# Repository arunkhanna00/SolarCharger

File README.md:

# Solar Charger

Using this PCB, you can charge a LiPo/Li-Ion battery with a solar panel and get a +5V voltage source. Additional features include:

- short circuit protection
- over charging/discharging protection
- MPPT

The voltage range for the input solar panel is 4-28 V.

The maximum current drawn from battery is around 800 mA

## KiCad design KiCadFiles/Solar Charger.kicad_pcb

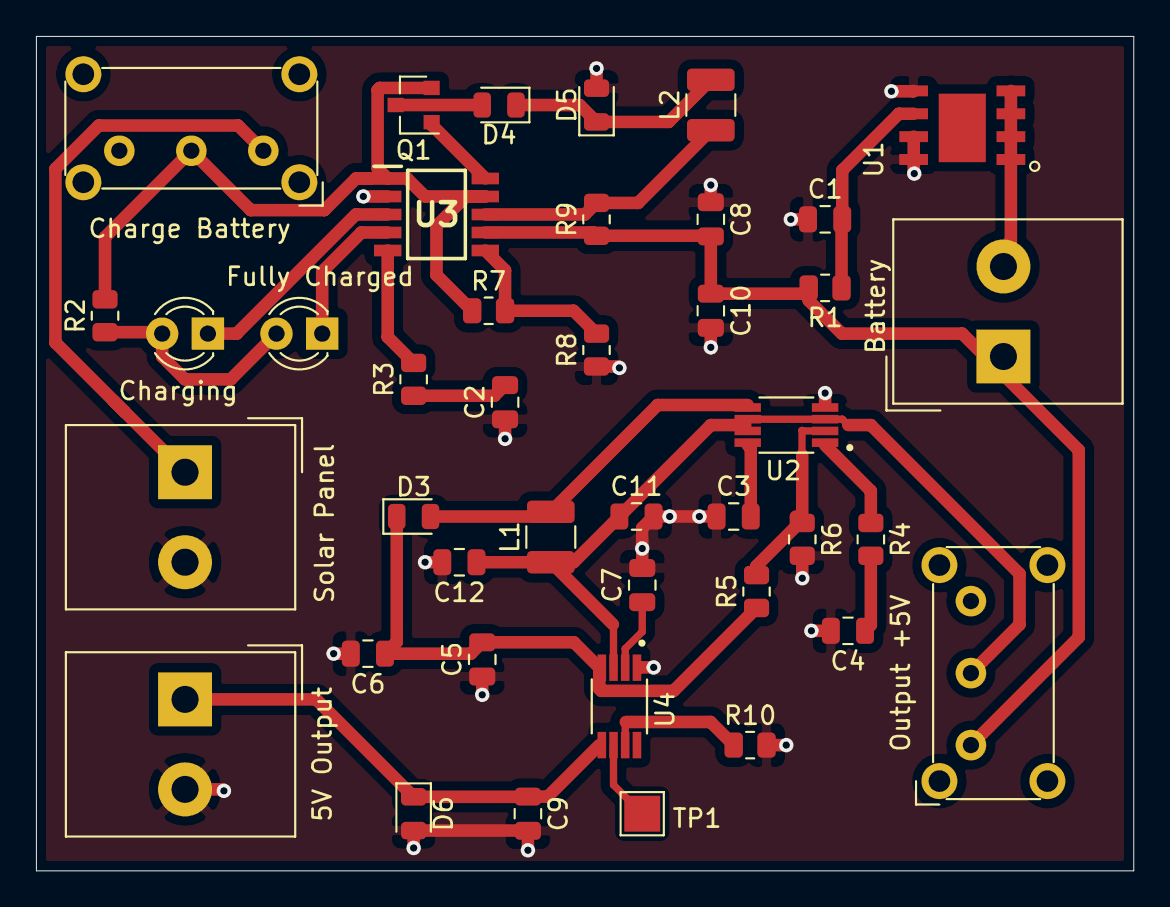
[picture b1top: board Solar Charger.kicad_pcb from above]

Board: 2 copper layers, 61.0 x 46.4 mm, 41 parts (0 on the bottom side), 27 nets.

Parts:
5V Output: Battery_Output; Altech_AK300_1x02_P5.00mm_45-Degree
Battery: Battery_Input; Altech_AK300_1x02_P5.00mm_45-Degree
C1: 0.1uF; C_0805_2012Metric
C2: 220nF; C_0805_2012Metric
C3: 100nF; C_0805_2012Metric
C4: 3.3nF; C_0805_2012Metric
C5, C6, C11: 10uF; C_0805_2012Metric
C7: 10nF; C_0805_2012Metric
C8: 4.7u; C_0805_2012Metric
C9: 100uF; C_0805_2012Metric
C10: 10u; C_0805_2012Metric
C12: 1uF; C_0805_2012Metric
Charge Battery: Charge; SW_E-Switch_EG1224_SPDT_Angled
Charging: RLED; LED_D3.0mm_FlatTop
D3, D4, D5, D6: D_Schottky; D_0805_2012Metric
Fully Charged: GLED; LED_D3.0mm_Clear
L1: 3.3uH; L_1210_3225Metric
L2: 82uH; L_1210_3225Metric
Output +5V: Battery Output; SW_E-Switch_EG1224_SPDT_Angled
Q1: AO3401A; SOT-23
R1, R2: 1k; R_0805_2012Metric
R3: 120; R_0805_2012Metric
R4: 13k; R_0805_2012Metric
R5: 54.9k; R_0805_2012Metric
R6: 18k; R_0805_2012Metric
R7: 2k; R_0805_2012Metric
R8: 28k; R_0805_2012Metric
R9: 0.05; R_0805_2012Metric
R10: 1.2k; R_0805_2012Metric
Solar Panel: Solar Panel; Altech_AK300_1x02_P5.00mm_45-Degree
TP1: TP; TestPoint_Pad_2.0x2.0mm
U1: XB8089; XB8089D
U2: TPS61085DGKR
U3: CN3791
U4: TPS259621; TPS61085DGKR

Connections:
+5V: 5V Output.1, C9.1, D6.1, U4.5
+Charge: L2.1, R9.2, U3.8
-BATT: Battery.2, U1.1, U1.2, U1.3, U1.4
-Charge: Battery.1, C8.2, C10.1, Output +5V.1, R1.2, R9.1, U3.7
Bat_Boost: C11.1, C12.1, L1.1, Output +5V.2, U2.3, U2.6, U2.7, U4.3
Charge: Charge Battery.2, Q1.2, R2.2, R7.1, U3.1, U3.9
GND: 5V Output.2, C1.1, C2.1, C3.1, C4.2, C5.1, C6.2, C7.2, C8.1, C9.2, C10.2, C11.2, C12.2, D5.2, D6.2, R6.2, R8.1, R10.2, Solar Panel.2, U1.5, U1.7, U1.8, U2.4, U3.2, U4.1
MOSFET: Q1.1, U3.10
unnamed: C1.2, R1.1, U1.6
unnamed: C2.2, R3.1
unnamed: C3.2, U2.8
unnamed: C4.1, R4.2
unnamed: C7.1, U4.2
unnamed: Charging.1, U3.3
unnamed: Charging.2, Fully Charged.2, R2.1
unnamed: Fully Charged.1, U3.4
unnamed: D3.2, L1.2, U2.5
unnamed: D4.1, D5.1, L2.2
unnamed: D4.2, Q1.3
unnamed: R3.2, U3.5
unnamed: R4.1, U2.1
unnamed: R5.2, R6.1, U2.2
unnamed: R7.2, R8.2, U3.6
unnamed: R10.1, U4.7
unnamed: TP1.1, U4.6
VDC: Charge Battery.1, Solar Panel.1
eFuse: C5.2, C6.1, D3.1, R5.1, U4.4

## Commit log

2021-08-30 added images
2021-08-30 added gerber
